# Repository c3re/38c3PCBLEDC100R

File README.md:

# 38c3PCBLEDC100R

The 38c3PCBLEDC100 is a Coaster for your drinks with option for LED and microcontroller upgrade. By stacking the coasters, you can also build nice blinky towers.

## Rev.0

### Electrical connections

Important: Do not power the board by USB and an external power supply at the same time!
The Din pin of the first LED is connected to pin D4 (GPIO2) of the Wemos D1 mini. Two of the mounting holes are connected to GND, two of the holes are connected to 5V. You can use this feature to stack multiple 38c3PCBLEDc100R Boards with brass spacers.

## License

The 38c3 Logo and blob was created by Robokid // Luis F. Masallera and Euler Void   
38c3PCBLEDC100R © 2024 by c3RE is licensed under CC BY 4.0. To view a copy of this license,   
visit http://creativecommons.org/licenses/by/4.0/

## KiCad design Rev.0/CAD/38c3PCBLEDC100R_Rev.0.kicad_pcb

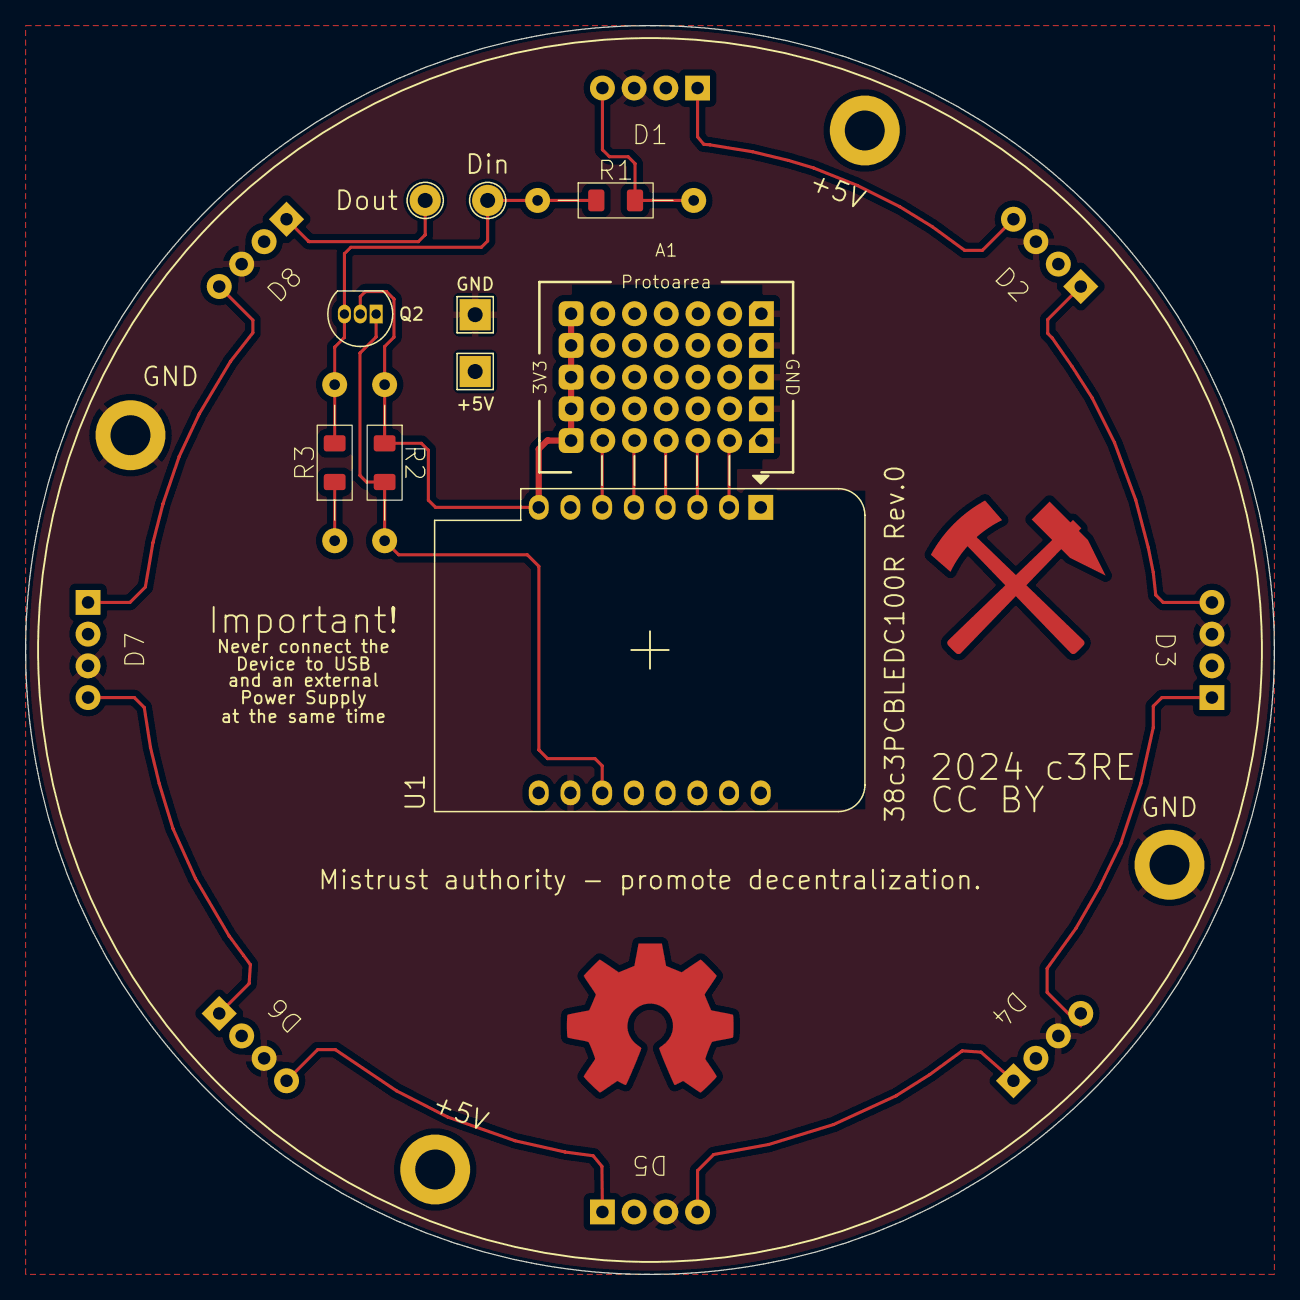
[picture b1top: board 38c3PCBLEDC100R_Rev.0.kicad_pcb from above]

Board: 2 copper layers, 100.0 x 100.0 mm, 22 parts (0 on the bottom side), 19 nets.

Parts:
+5V: +5V; MountingHole_3.2mm_M3_DIN965_Pad
+5V#2: +5V; TestPoint_THTPad_2.5x2.5mm_Drill1.2mm
A1: Protoarea
D1, D2, D3, D4, D5, D6, D7, D8: WS2812D-F5; WS2812_THT
Din: Din; TestPoint_THTPad_D2.5mm_Drill1.2mm
Dout: Dout; TestPoint_THTPad_D2.5mm_Drill1.2mm
GND: GND; MountingHole_3.2mm_M3_DIN965_Pad
GND#2: GND; TestPoint_THTPad_2.5x2.5mm_Drill1.2mm
GND#3: GND; MountingHole_3.2mm_M3_DIN965_Pad
H1: +5V; MountingHole_3.2mm_M3_DIN965_Pad
Q2: ZVNL110A; TO-92_Inline
R1: 100; 1206_combi_handsolder
R2, R3: 10k; 1206_combi_handsolder
U1: WeMos_D1_mini; WEMOS_D1_mini_light

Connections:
+5V: +5V.1, +5V#2.1, D1.2 (VCC), D2.2 (VCC), D3.2 (VCC), D4.2 (VCC), D5.2 (VCC), D6.2 (VCC), D7.2 (VCC), D8.2 (VCC), H1.1, R3.1, U1.9 (5V)
/Din: Din.1, Q2.3 (D), R1.1, R3.2
/Dout: D8.1 (DOUT), Dout.1
GND: A1.7 (GND), D1.3 (GND), D2.3 (GND), D3.3 (GND), D4.3 (GND), D5.3 (GND), D6.3 (GND), D7.3 (GND), D8.3 (GND), GND.1, GND#2.1, GND#3.1, U1.10 (GND)
unnamed: A1.8 (Vin), Q2.2 (G), R2.1, U1.8 (3V3)
unnamed: D1.4 (DIN), R1.2
unnamed: D1.1 (DOUT), D2.4 (DIN)
unnamed: D2.1 (DOUT), D3.4 (DIN)
unnamed: D3.1 (DOUT), D4.4 (DIN)
unnamed: D4.1 (DOUT), D5.4 (DIN)
unnamed: D5.1 (DOUT), D6.4 (DIN)
unnamed: D6.1 (DOUT), D7.4 (DIN)
unnamed: D7.1 (DOUT), D8.4 (DIN)
unnamed: Q2.1 (S), R2.2, U1.11 (D4)
unnamed: A1.6, U1.2 (A0)
unnamed: A1.5, U1.3 (D0)
unnamed: A1.3, U1.5 (MISO/D6)
unnamed: A1.2, U1.6 (MOSI/D7)
unnamed: A1.4, U1.4 (SCK/D5)

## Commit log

2024-11-24 Added CAD Files
2024-11-24 Added some basic Content
2024-11-24 BOM added
2024-11-24 Typo fixed
2024-12-29 upload construction inlay
2025-10-22 some files added
2025-10-22 picture linked to readme.md
2025-10-22 Updateted .gitignore
2025-10-22 Deleted some files
2025-10-22 Renamed some files
2025-10-22 Updated the README.md
2025-10-22 Typo
